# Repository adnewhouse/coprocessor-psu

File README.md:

# coprocessor-psu

- 6-15V input, 19V output at up to 5A
- Supplies power to onboard vision co-proccesor
- Custom circuit powered by 10A breaker on PDH
- Robust input protection

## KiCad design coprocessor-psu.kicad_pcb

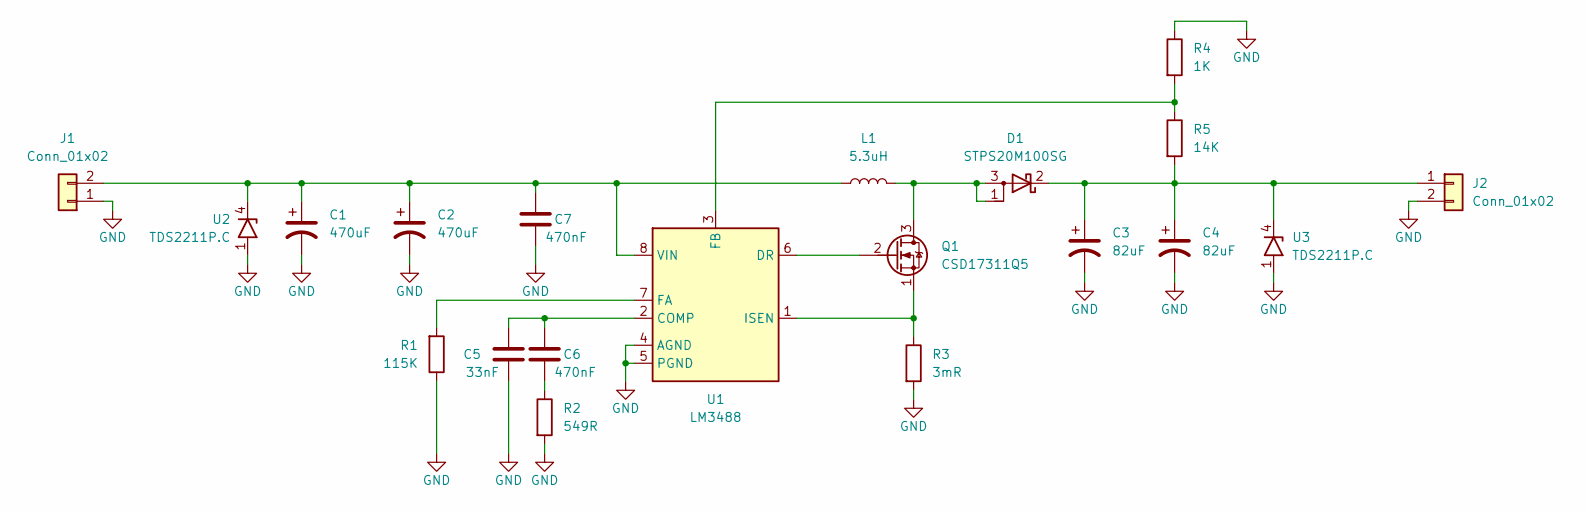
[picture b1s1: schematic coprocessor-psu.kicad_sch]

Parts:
C1, C2: 470uF; CP_Elec_8x10.5; MPN EEE-FN1E471UV
C3, C4: 82uF; CP_Elec_8x11.9; MPN 35SVPF82M
C5: 33nF; C_0805_2012Metric; MPN CGA4J1C0G2A333J125AE
C6, C7: 470nF; C_0805_2012Metric; MPN CGA4J3X7R1H474K125AE
D1: STPS20M100SG; TO-263-2; MPN STPS20M100SG
J1: Conn_01x02; TerminalBlock_Phoenix_PT-1,5-2-5.0-H_1x02_P5.00mm_Horizontal
J2: Conn_01x02
L1: 5.3uH; XAL1580; MPN XAL1580-532MED
Q1: CSD17311Q5; VSONP-8-1EP_5x6_P1.27mm; MPN CSD17311Q5
R1: 115K; R_0805_2012Metric
R2: 549R; R_0805_2012Metric
R3: 3mR; R_0612_1632Metric; MPN WSL06123L000FEA
R4: 1K; R_0805_2012Metric
R5: 14K; R_0805_2012Metric
U1: LM3488; VSSOP-8_3.0x3.0mm_P0.65mm; MPN LM3488MM
U2, U3: TDS2211P.C; DFN-6_1.6x1.6

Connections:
GND: C1.2, C2.2, C3.2, C4.2, C5.1, C7.1, J1.1, J2.2, R1.1, R2.2, R3.2, R4.1, U1.4 (AGND), U1.5 (PGND), U2.1, U2.2, U2.3, U3.1, U3.2, U3.3
unnamed: C1.1, C2.1, C7.2, J1.2, L1.1, U1.8 (VIN), U2.4, U2.5, U2.6
unnamed: C3.1, C4.1, D1.2 (K), J2.1, R5.2, U3.4, U3.5, U3.6
unnamed: C5.2, C6.2, U1.2 (COMP)
unnamed: C6.1, R2.1
unnamed: D1.1 (A), D1.3 (A), L1.2, Q1.3 (D)
unnamed: Q1.1 (S), R3.1, U1.1 (ISEN)
unnamed: Q1.2 (G), U1.6 (DR)
unnamed: R1.2, U1.7 (FA)
unnamed: R4.2, R5.1, U1.3 (FB)

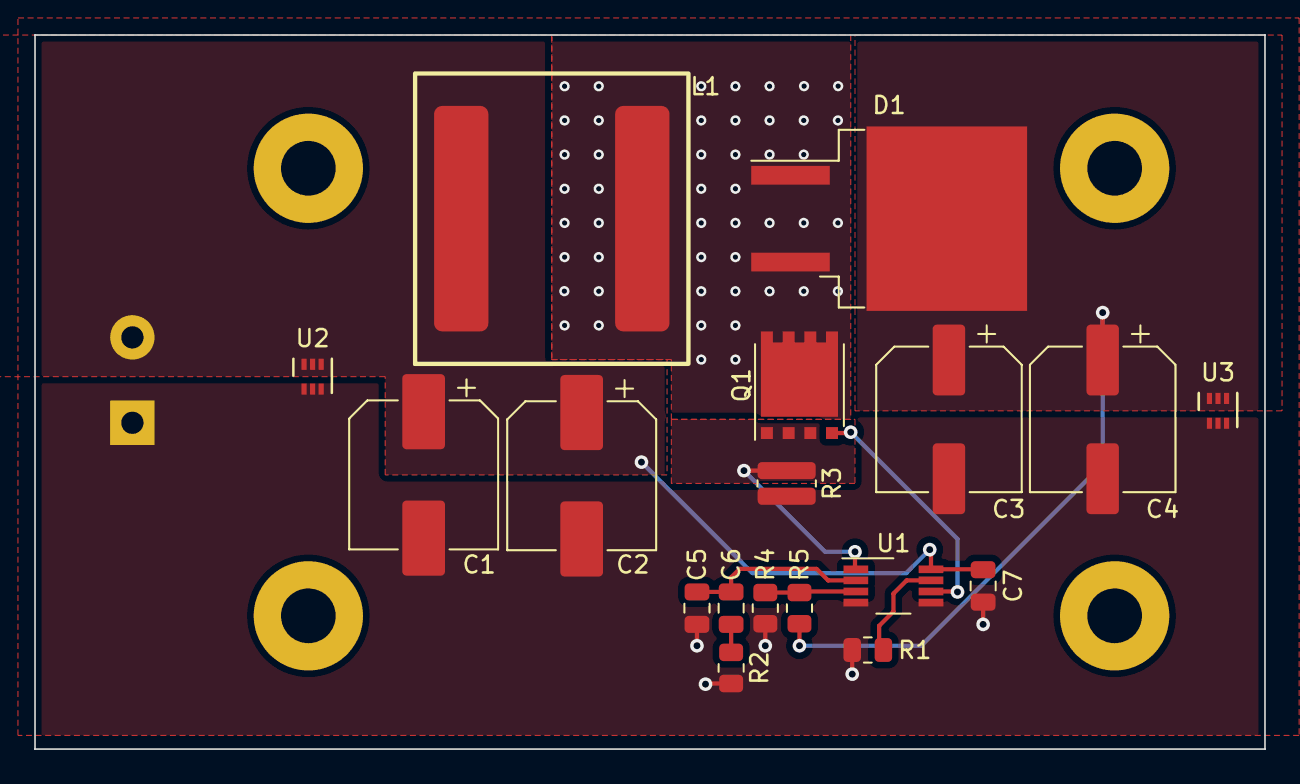
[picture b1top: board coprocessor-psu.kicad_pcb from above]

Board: 2 copper layers, 72.0 x 41.8 mm, 19 parts (1 on the bottom side), 10 nets.

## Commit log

2023-01-11 some more details
2023-01-15 Add 3d model, finish layout pending type-c plug study
2023-01-24 add 3d models
